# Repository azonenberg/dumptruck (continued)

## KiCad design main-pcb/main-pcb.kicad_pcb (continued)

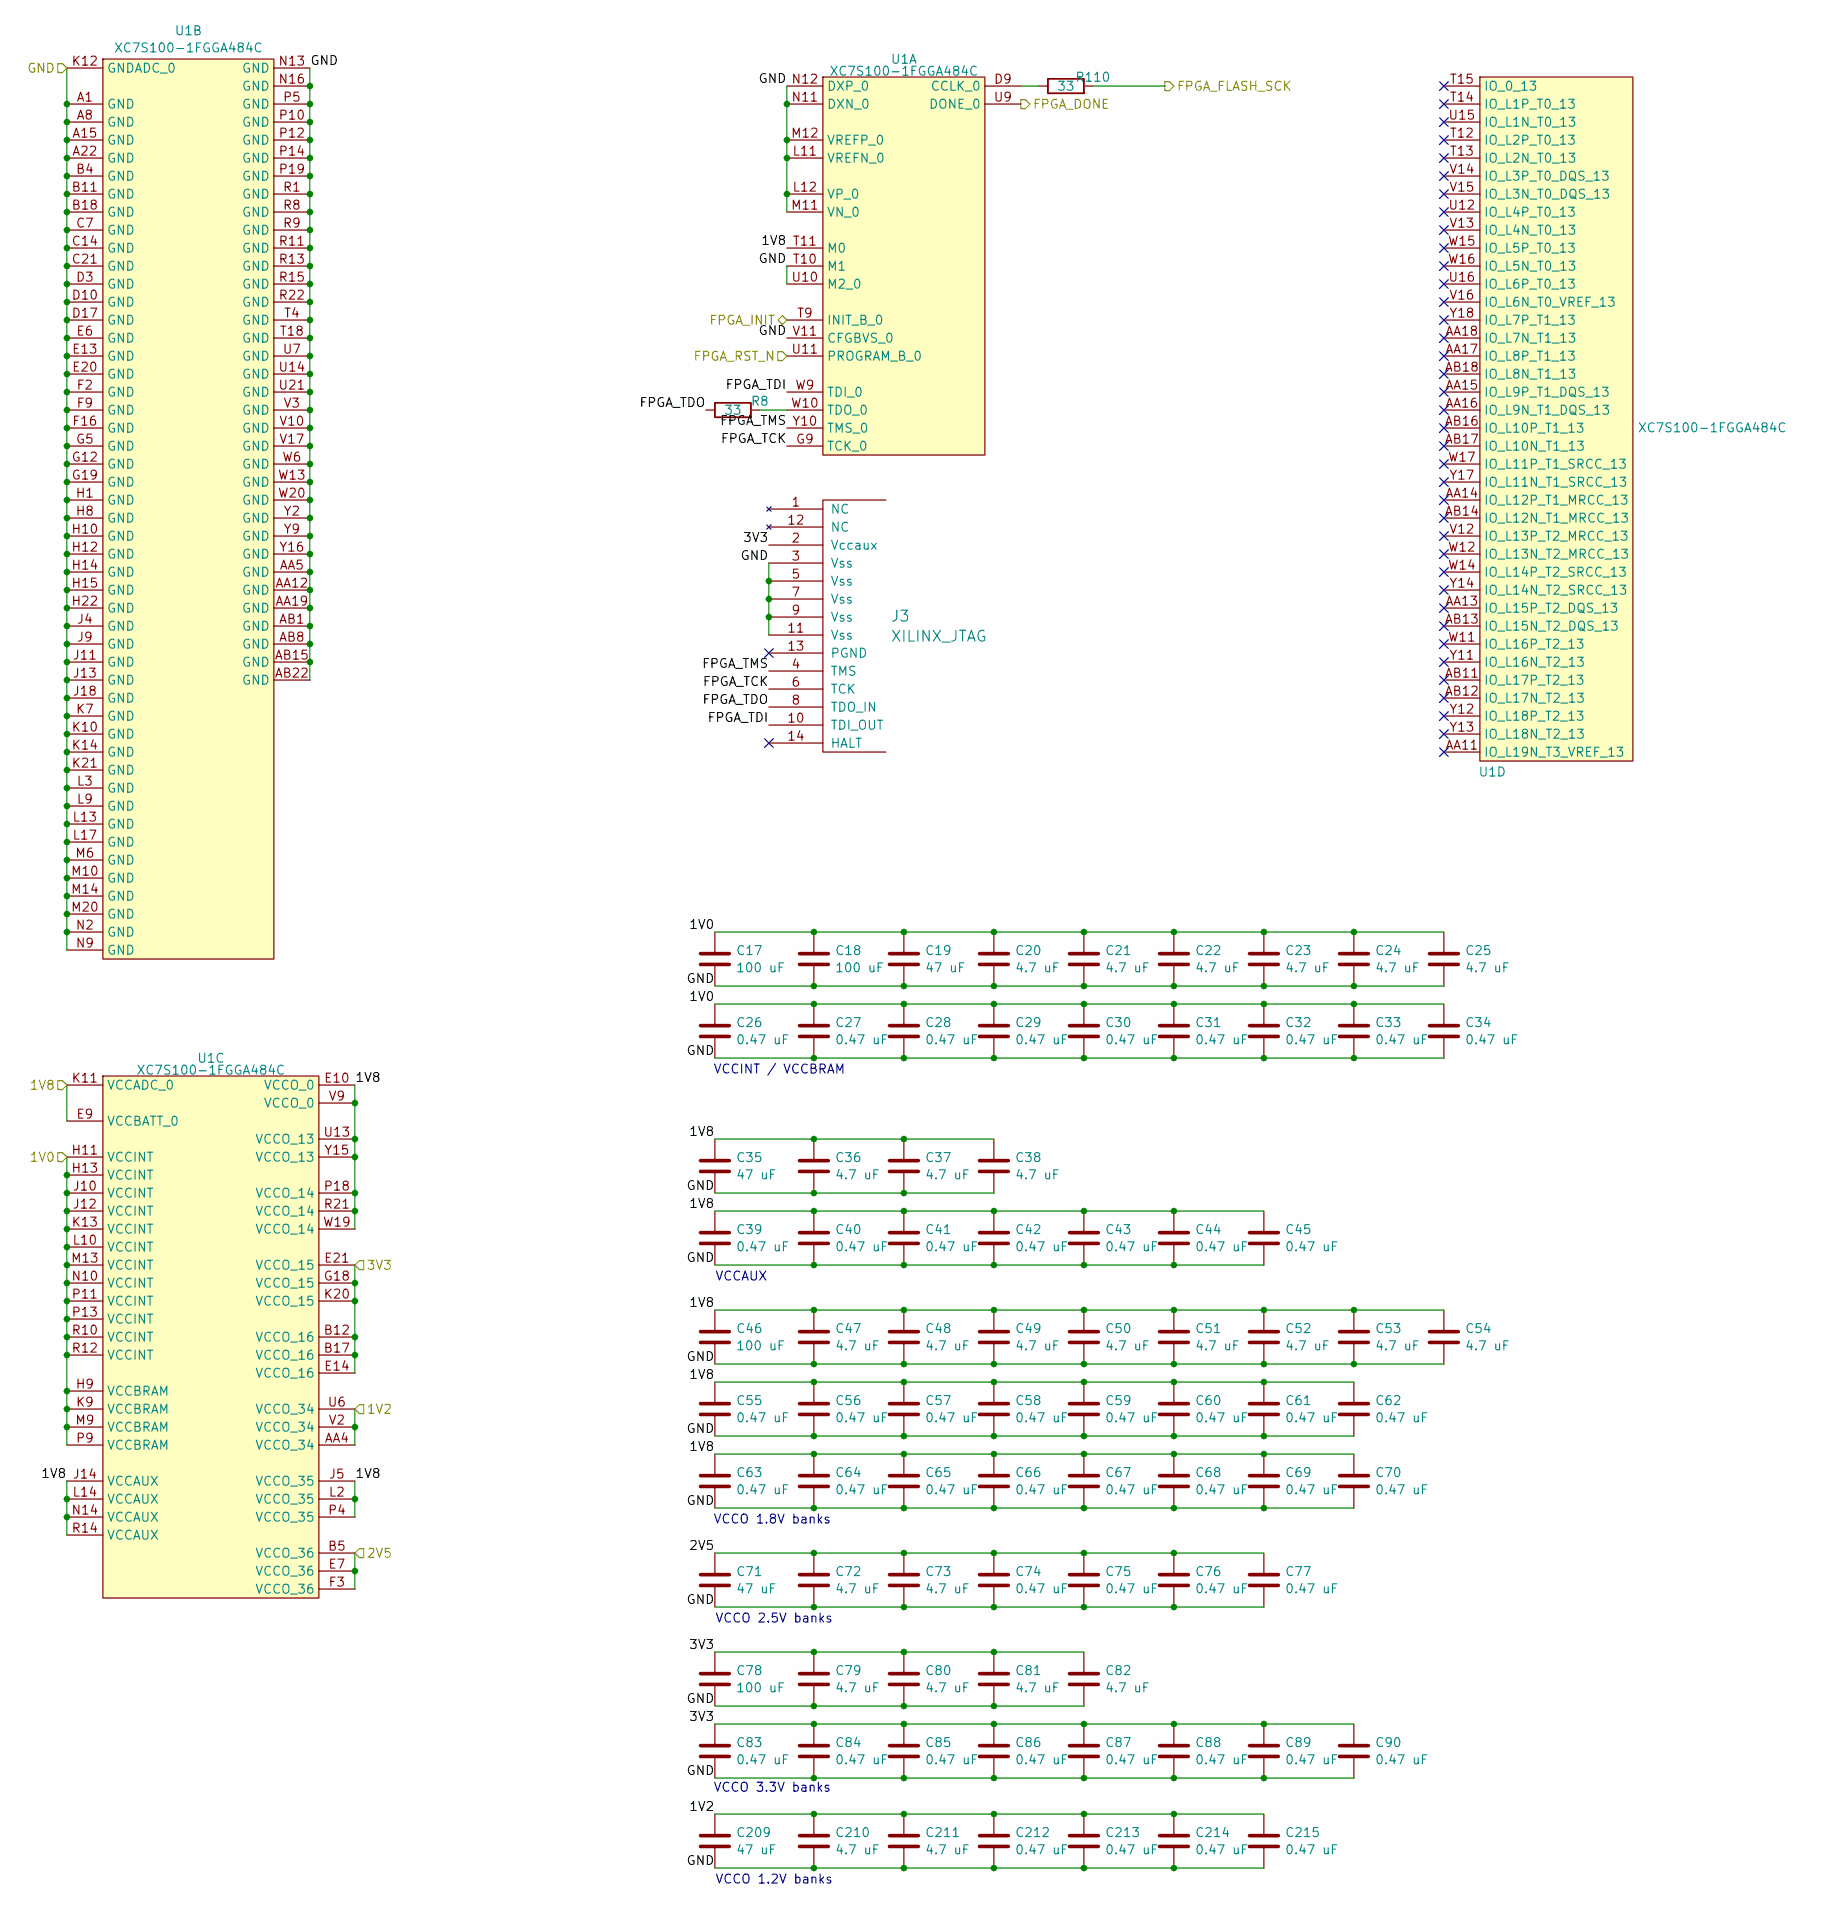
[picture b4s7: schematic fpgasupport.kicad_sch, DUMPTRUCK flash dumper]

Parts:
C17, C18, C46: 100 uF; EIA_1206_CAP_NOSILK
C19, C35, C71, C209: 47 uF; EIA_1210_CAP_NOSILK
C20, C21, C22, C23, C24, C25, C36, C37, C38, C47, C48, C49, C50, C51, C52, C53, C54, C72, C73, C79, C80, C81, C82, C210, C211: 4.7 uF; EIA_0603_CAP_NOSILK
C26, C27, C28, C29, C30, C31, C32, C33, C34, C39, C40, C41, C42, C43, C44, C45, C55, C56, C57, C58, C59, C60, C61, C62, C63, C64, C65, C66, C67, C68, C69, C70, C74, C75, C76, C77, C83, C84, C85, C86, C87, C88, C89, C90, C212, C213, C214, C215: 0.47 uF; EIA_0402_CAP_NOSILK
C78: 100 uF; EIA_1210_CAP_NOSILK
J3: XILINX_JTAG; XILINX_JTAG_PTH_MOLEX_0878311420
R8, R110: 33; EIA_0402_RES_NOSILK
U1: XC7S100-1FGGA484C; BGA_484_22x22_FULLARRAY_1MM

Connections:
/1V0: C17.1, C18.1, C19.1, C20.1, C21.1, C22.1, C23.1, C24.1, C25.1, C26.1, C27.1, C28.1, C29.1, C30.1, C31.1, C32.1, C33.1, C34.1, U1.H9 (VCCBRAM), U1.H11 (VCCINT), U1.H13 (VCCINT), U1.J10 (VCCINT), U1.J12 (VCCINT), U1.K9 (VCCBRAM), U1.K13 (VCCINT), U1.L10 (VCCINT), U1.M9 (VCCBRAM), U1.M13 (VCCINT), U1.N10 (VCCINT), U1.P9 (VCCBRAM), U1.P11 (VCCINT), U1.P13 (VCCINT), U1.R10 (VCCINT), U1.R12 (VCCINT); also elsewhere on the board
/1V2: C209.1, C210.1, C211.1, C212.1, C213.1, C214.1, C215.1, U1.AA4 (VCCO_34), U1.U6 (VCCO_34), U1.V2 (VCCO_34); also elsewhere on the board
/1V8: C35.1, C36.1, C37.1, C38.1, C39.1, C40.1, C41.1, C42.1, C43.1, C44.1, C45.1, C46.1, C47.1, C48.1, C49.1, C50.1, C51.1, C52.1, C53.1, C54.1, C55.1, C56.1, C57.1, C58.1, C59.1, C60.1, C61.1, C62.1, C63.1, C64.1, C65.1, C66.1, C67.1, C68.1, C69.1, C70.1, U1.E9 (VCCBATT_0), U1.E10 (VCCO_0), U1.J5 (VCCO_35), U1.J14 (VCCAUX), U1.K11 (VCCADC_0), U1.L2 (VCCO_35), U1.L14 (VCCAUX), U1.N14 (VCCAUX), U1.P4 (VCCO_35), U1.P18 (VCCO_14), U1.R14 (VCCAUX), U1.R21 (VCCO_14), U1.T11 (M0), U1.U13 (VCCO_13), U1.V9 (VCCO_0), U1.W19 (VCCO_14), U1.Y15 (VCCO_13); also elsewhere on the board
/2V5: C71.1, C72.1, C73.1, C74.1, C75.1, C76.1, C77.1, U1.B5 (VCCO_36), U1.E7 (VCCO_36), U1.F3 (VCCO_36); also elsewhere on the board
/3V3: C78.1, C79.1, C80.1, C81.1, C82.1, C83.1, C84.1, C85.1, C86.1, C87.1, C88.1, C89.1, C90.1, J3.2 (Vccaux), U1.B12 (VCCO_16), U1.B17 (VCCO_16), U1.E14 (VCCO_16), U1.E21 (VCCO_15), U1.G18 (VCCO_15), U1.K20 (VCCO_15); also elsewhere on the board
/FLASH_SCK: R110.2; also elsewhere on the board
/FPGA support/FPGA_INIT: U1.T9 (INIT_B_0); also elsewhere on the board
/FPGA support/FPGA_RST_N: U1.U11 (PROGRAM_B_0); also elsewhere on the board
/FPGA support/FPGA_TCK: J3.6 (TCK), U1.G9 (TCK_0)
/FPGA support/FPGA_TDI: J3.10 (TDI_OUT), U1.W9 (TDI_0)
/FPGA support/FPGA_TDO: J3.8 (TDO_IN), R8.1
/FPGA support/FPGA_TMS: J3.4 (TMS), U1.Y10 (TMS_0)
/FPGA_DONE: U1.U9 (DONE_0); also elsewhere on the board
/GND: C17.2, C18.2, C19.2, C20.2, C21.2, C22.2, C23.2, C24.2, C25.2, C26.2, C27.2, C28.2, C29.2, C30.2, C31.2, C32.2, C33.2, C34.2, C35.2, C36.2, C37.2, C38.2, C39.2, C40.2, C41.2, C42.2, C43.2, C44.2, C45.2, C46.2, C47.2, C48.2, C49.2, C50.2, C51.2, C52.2, C53.2, C54.2, C55.2, C56.2, C57.2, C58.2, C59.2, C60.2, C61.2, C62.2, C63.2, C64.2, C65.2, C66.2, C67.2, C68.2, C69.2, C70.2, C71.2, C72.2, C73.2, C74.2, C75.2, C76.2, C77.2, C78.2, C79.2, C80.2, C81.2, C82.2, C83.2, C84.2, C85.2, C86.2, C87.2, C88.2, C89.2, C90.2, C209.2, C210.2, C211.2, C212.2, C213.2, C214.2, C215.2, J3.3 (Vss), J3.5 (Vss), J3.7 (Vss), J3.9 (Vss), J3.11 (Vss), U1.A1 (GND), U1.A8 (GND), U1.A15 (GND), U1.A22 (GND), U1.AA5 (GND), U1.AA12 (GND), U1.AA19 (GND), U1.AB1 (GND), U1.AB8 (GND), U1.AB15 (GND), U1.AB22 (GND), U1.B4 (GND), U1.B11 (GND), U1.B18 (GND), U1.C7 (GND), U1.C14 (GND), U1.C21 (GND), U1.D3 (GND), U1.D10 (GND), U1.D17 (GND), U1.E6 (GND), U1.E13 (GND), U1.E20 (GND), U1.F2 (GND), U1.F9 (GND), U1.F16 (GND), U1.G5 (GND), U1.G12 (GND), U1.G19 (GND), U1.H1 (GND), U1.H8 (GND), U1.H10 (GND), U1.H12 (GND), U1.H14 (GND), U1.H15 (GND), U1.H22 (GND), U1.J4 (GND), U1.J9 (GND), U1.J11 (GND), U1.J13 (GND), U1.J18 (GND), U1.K7 (GND), U1.K10 (GND), U1.K12 (GNDADC_0), U1.K14 (GND), U1.K21 (GND), U1.L3 (GND), U1.L9 (GND), U1.L11 (VREFN_0), U1.L12 (VP_0), U1.L13 (GND), U1.L17 (GND), U1.M6 (GND), U1.M10 (GND), U1.M11 (VN_0), U1.M12 (VREFP_0), U1.M14 (GND), U1.M20 (GND), U1.N2 (GND), U1.N9 (GND), U1.N11 (DXN_0), U1.N12 (DXP_0), U1.N13 (GND), U1.N16 (GND), U1.P5 (GND), U1.P10 (GND), U1.P12 (GND), U1.P14 (GND), U1.P19 (GND), U1.R1 (GND), U1.R8 (GND), U1.R9 (GND), U1.R11 (GND), U1.R13 (GND), U1.R15 (GND), U1.R22 (GND), U1.T4 (GND), U1.T10 (M1), U1.T18 (GND), U1.U7 (GND), U1.U10 (M2_0), U1.U14 (GND), U1.U21 (GND), U1.V3 (GND), U1.V10 (GND), U1.V11 (CFGBVS_0), U1.V17 (GND), U1.W6 (GND), U1.W13 (GND), U1.W20 (GND), U1.Y2 (GND), U1.Y9 (GND), U1.Y16 (GND); also elsewhere on the board
unnamed: R110.1, U1.D9 (CCLK_0)
unnamed: R8.2, U1.W10 (TDO_0)

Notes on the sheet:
VCCO 1.2V banks
VCCO 2.5V banks
VCCAUX
VCCO 3.3V banks
VCCINT / VCCBRAM
VCCO 1.8V banks

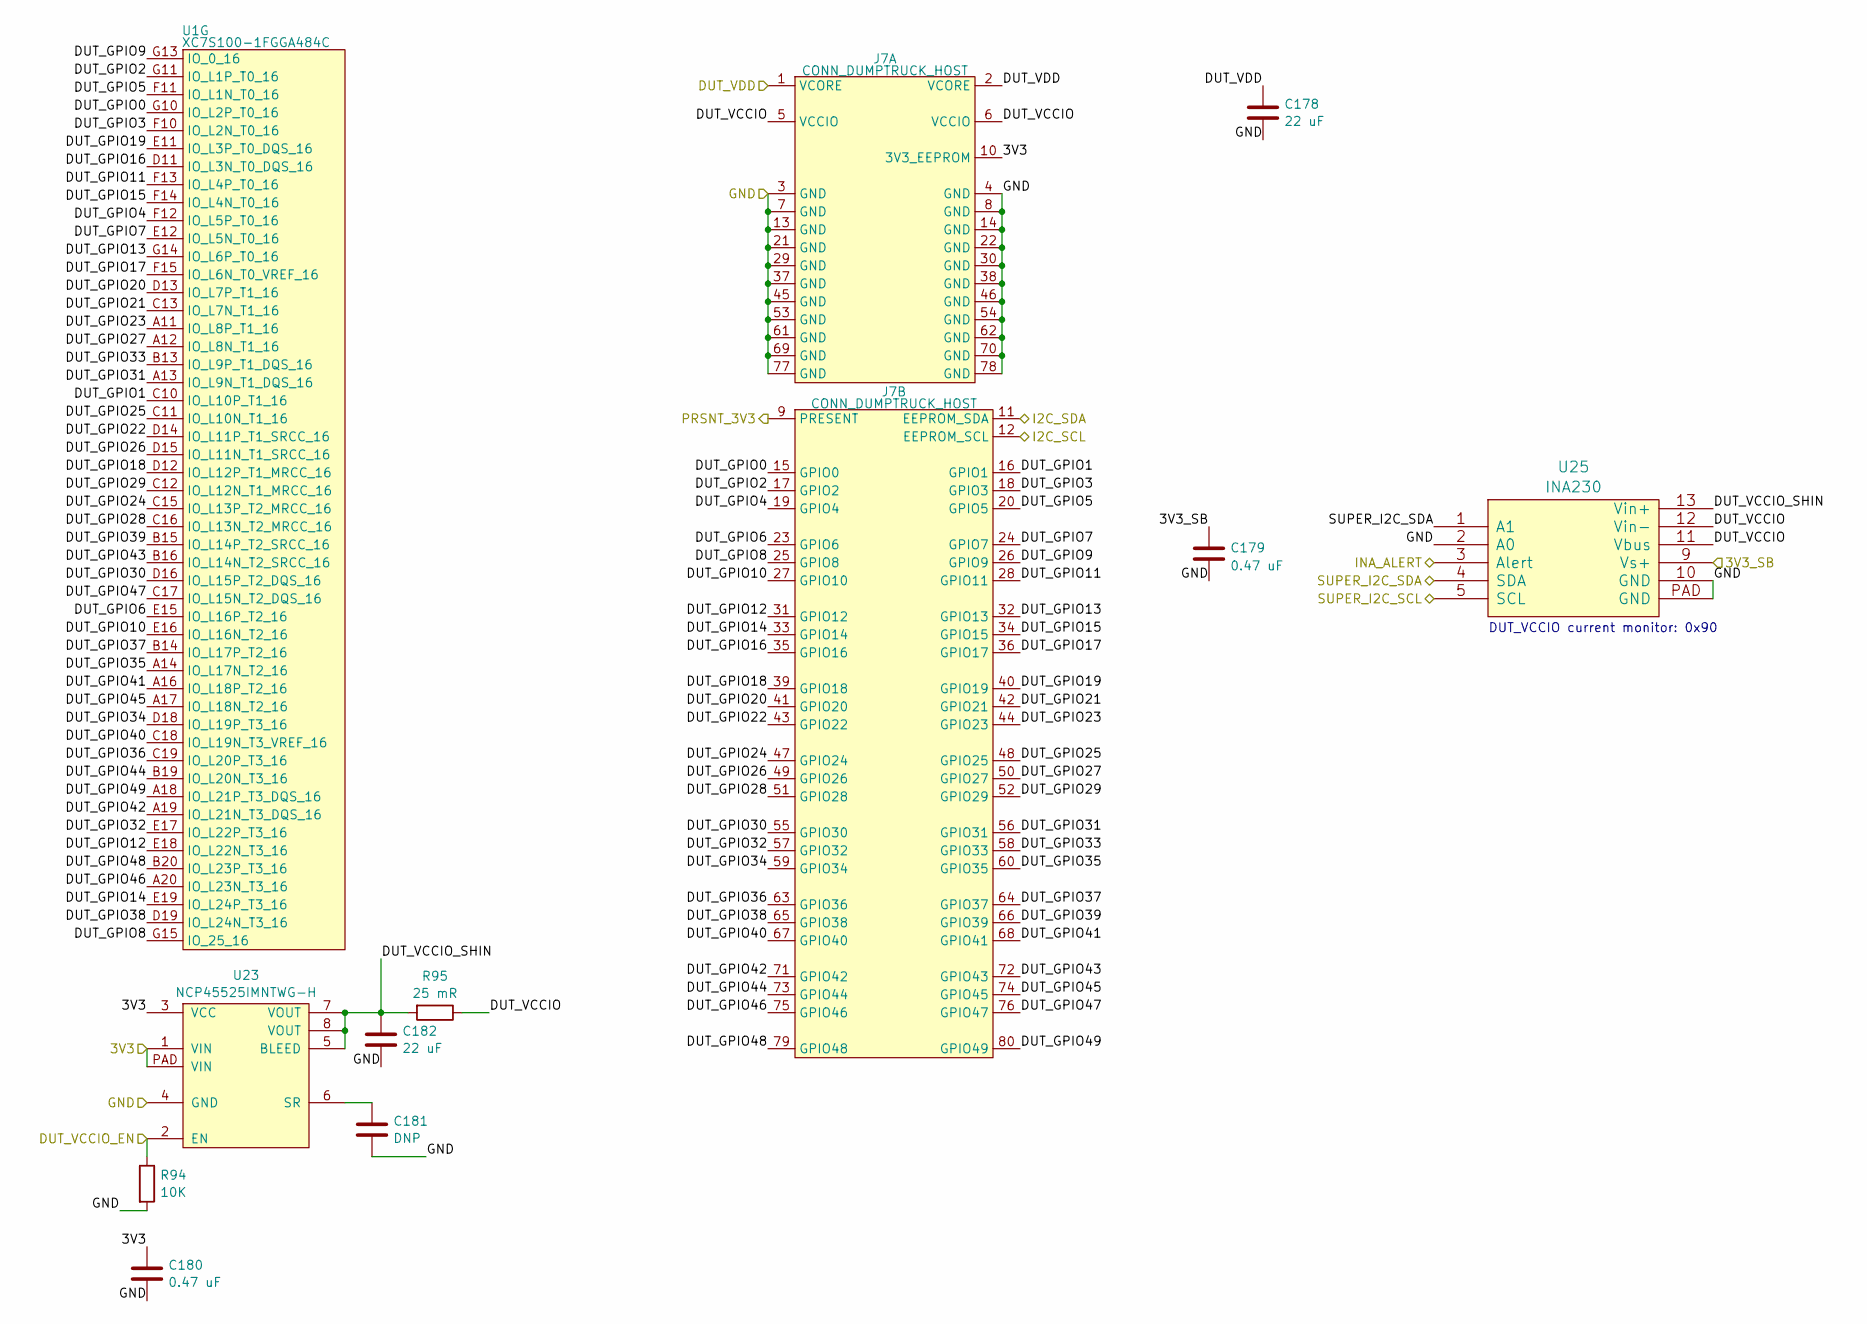
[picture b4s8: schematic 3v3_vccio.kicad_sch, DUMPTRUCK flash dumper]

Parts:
C178: 22 uF; EIA_1206_CAP_NOSILK
C179, C180: 0.47 uF; EIA_0402_CAP_NOSILK
C181: DNP; EIA_0402_CAP_NOSILK
C182: 22 uF; EIA_1210_CAP_NOSILK
J7: CONN_DUMPTRUCK_HOST; CONN_SAMTEC_BTE-040-01-F-D-A-K
R94: 10K; EIA_0402_RES_NOSILK
R95: 25 mR; EIA_0402_RES_NOSILK
U1: XC7S100-1FGGA484C; BGA_484_22x22_FULLARRAY_1MM
U23: NCP45525IMNTWG-H; DFN_8_0.5MM_2x2MM
U25: INA230; QFN_16_0.5MM_3x3MM

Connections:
/3V3: C180.1, J7.10 (3V3_EEPROM), U23.1 (VIN), U23.3 (VCC), U23.PAD (VIN); also elsewhere on the board
/3V3 VCCIO socket/DUT_GPIO0: J7.15 (GPIO0), U1.G10 (IO_L2P_T0_16)
/3V3 VCCIO socket/DUT_GPIO1: J7.16 (GPIO1), U1.C10 (IO_L10P_T1_16)
/3V3 VCCIO socket/DUT_GPIO2: J7.17 (GPIO2), U1.G11 (IO_L1P_T0_16)
/3V3 VCCIO socket/DUT_GPIO3: J7.18 (GPIO3), U1.F10 (IO_L2N_T0_16)
/3V3 VCCIO socket/DUT_GPIO4: J7.19 (GPIO4), U1.F12 (IO_L5P_T0_16)
/3V3 VCCIO socket/DUT_GPIO5: J7.20 (GPIO5), U1.F11 (IO_L1N_T0_16)
/3V3 VCCIO socket/DUT_GPIO6: J7.23 (GPIO6), U1.E15 (IO_L16P_T2_16)
/3V3 VCCIO socket/DUT_GPIO7: J7.24 (GPIO7), U1.E12 (IO_L5N_T0_16)
/3V3 VCCIO socket/DUT_GPIO8: J7.25 (GPIO8), U1.G15 (IO_25_16)
/3V3 VCCIO socket/DUT_GPIO9: J7.26 (GPIO9), U1.G13 (IO_0_16)
/3V3 VCCIO socket/DUT_GPIO10: J7.27 (GPIO10), U1.E16 (IO_L16N_T2_16)
/3V3 VCCIO socket/DUT_GPIO11: J7.28 (GPIO11), U1.F13 (IO_L4P_T0_16)
/3V3 VCCIO socket/DUT_GPIO12: J7.31 (GPIO12), U1.E18 (IO_L22N_T3_16)
/3V3 VCCIO socket/DUT_GPIO13: J7.32 (GPIO13), U1.G14 (IO_L6P_T0_16)
/3V3 VCCIO socket/DUT_GPIO14: J7.33 (GPIO14), U1.E19 (IO_L24P_T3_16)
/3V3 VCCIO socket/DUT_GPIO15: J7.34 (GPIO15), U1.F14 (IO_L4N_T0_16)
/3V3 VCCIO socket/DUT_GPIO16: J7.35 (GPIO16), U1.D11 (IO_L3N_T0_DQS_16)
/3V3 VCCIO socket/DUT_GPIO17: J7.36 (GPIO17), U1.F15 (IO_L6N_T0_VREF_16)
/3V3 VCCIO socket/DUT_GPIO18: J7.39 (GPIO18), U1.D12 (IO_L12P_T1_MRCC_16)
/3V3 VCCIO socket/DUT_GPIO19: J7.40 (GPIO19), U1.E11 (IO_L3P_T0_DQS_16)
/3V3 VCCIO socket/DUT_GPIO20: J7.41 (GPIO20), U1.D13 (IO_L7P_T1_16)
/3V3 VCCIO socket/DUT_GPIO21: J7.42 (GPIO21), U1.C13 (IO_L7N_T1_16)
/3V3 VCCIO socket/DUT_GPIO22: J7.43 (GPIO22), U1.D14 (IO_L11P_T1_SRCC_16)
/3V3 VCCIO socket/DUT_GPIO23: J7.44 (GPIO23), U1.A11 (IO_L8P_T1_16)
/3V3 VCCIO socket/DUT_GPIO24: J7.47 (GPIO24), U1.C15 (IO_L13P_T2_MRCC_16)
/3V3 VCCIO socket/DUT_GPIO25: J7.48 (GPIO25), U1.C11 (IO_L10N_T1_16)
/3V3 VCCIO socket/DUT_GPIO26: J7.49 (GPIO26), U1.D15 (IO_L11N_T1_SRCC_16)
/3V3 VCCIO socket/DUT_GPIO27: J7.50 (GPIO27), U1.A12 (IO_L8N_T1_16)
/3V3 VCCIO socket/DUT_GPIO28: J7.51 (GPIO28), U1.C16 (IO_L13N_T2_MRCC_16)
/3V3 VCCIO socket/DUT_GPIO29: J7.52 (GPIO29), U1.C12 (IO_L12N_T1_MRCC_16)
/3V3 VCCIO socket/DUT_GPIO30: J7.55 (GPIO30), U1.D16 (IO_L15P_T2_DQS_16)
/3V3 VCCIO socket/DUT_GPIO31: J7.56 (GPIO31), U1.A13 (IO_L9N_T1_DQS_16)
/3V3 VCCIO socket/DUT_GPIO32: J7.57 (GPIO32), U1.E17 (IO_L22P_T3_16)
/3V3 VCCIO socket/DUT_GPIO33: J7.58 (GPIO33), U1.B13 (IO_L9P_T1_DQS_16)
/3V3 VCCIO socket/DUT_GPIO34: J7.59 (GPIO34), U1.D18 (IO_L19P_T3_16)
/3V3 VCCIO socket/DUT_GPIO35: J7.60 (GPIO35), U1.A14 (IO_L17N_T2_16)
/3V3 VCCIO socket/DUT_GPIO36: J7.63 (GPIO36), U1.C19 (IO_L20P_T3_16)
/3V3 VCCIO socket/DUT_GPIO37: J7.64 (GPIO37), U1.B14 (IO_L17P_T2_16)
/3V3 VCCIO socket/DUT_GPIO38: J7.65 (GPIO38), U1.D19 (IO_L24N_T3_16)
/3V3 VCCIO socket/DUT_GPIO39: J7.66 (GPIO39), U1.B15 (IO_L14P_T2_SRCC_16)
/3V3 VCCIO socket/DUT_GPIO40: J7.67 (GPIO40), U1.C18 (IO_L19N_T3_VREF_16)
/3V3 VCCIO socket/DUT_GPIO41: J7.68 (GPIO41), U1.A16 (IO_L18P_T2_16)
/3V3 VCCIO socket/DUT_GPIO42: J7.71 (GPIO42), U1.A19 (IO_L21N_T3_DQS_16)
/3V3 VCCIO socket/DUT_GPIO43: J7.72 (GPIO43), U1.B16 (IO_L14N_T2_SRCC_16)
/3V3 VCCIO socket/DUT_GPIO44: J7.73 (GPIO44), U1.B19 (IO_L20N_T3_16)
/3V3 VCCIO socket/DUT_GPIO45: J7.74 (GPIO45), U1.A17 (IO_L18N_T2_16)
/3V3 VCCIO socket/DUT_GPIO46: J7.75 (GPIO46), U1.A20 (IO_L23N_T3_16)
/3V3 VCCIO socket/DUT_GPIO47: J7.76 (GPIO47), U1.C17 (IO_L15N_T2_DQS_16)
/3V3 VCCIO socket/DUT_GPIO48: J7.79 (GPIO48), U1.B20 (IO_L23P_T3_16)
/3V3 VCCIO socket/DUT_GPIO49: J7.80 (GPIO49), U1.A18 (IO_L21P_T3_DQS_16)
/3V3 VCCIO socket/DUT_VCCIO: J7.5 (VCCIO), J7.6 (VCCIO), R95.1, U25.11 (Vbus), U25.12 (Vin-)
/3V3 VCCIO socket/DUT_VCCIO_SHIN: C182.1, R95.2, U23.5 (BLEED), U23.7 (VOUT), U23.8 (VOUT), U25.13 (Vin+)
/3V3_SB: C179.1, U25.9 (Vs+); also elsewhere on the board
/DUT_VCCIO_EN: R94.1, U23.2 (EN); also elsewhere on the board
/DUT_VDD: C178.1, J7.1 (VCORE), J7.2 (VCORE); also elsewhere on the board
/GND: C178.2, C179.2, C180.2, C181.2, C182.2, J7.3 (GND), J7.4 (GND), J7.7 (GND), J7.8 (GND), J7.13 (GND), J7.14 (GND), J7.21 (GND), J7.22 (GND), J7.29 (GND), J7.30 (GND), J7.37 (GND), J7.38 (GND), J7.45 (GND), J7.46 (GND), J7.53 (GND), J7.54 (GND), J7.61 (GND), J7.62 (GND), J7.69 (GND), J7.70 (GND), J7.77 (GND), J7.78 (GND), R94.2, U23.4 (GND), U25.2 (A0), U25.10 (GND), U25.PAD (GND); also elsewhere on the board
/I2C_SCL: J7.12 (EEPROM_SCL); also elsewhere on the board
/I2C_SDA: J7.11 (EEPROM_SDA); also elsewhere on the board
/INA_ALERT: U25.3 (Alert); also elsewhere on the board
/PRSNT_3V3: J7.9 (PRESENT); also elsewhere on the board
/SUPER_I2C_SCL: U25.5 (SCL); also elsewhere on the board
/SUPER_I2C_SDA: U25.1 (A1), U25.4 (SDA); also elsewhere on the board
unnamed: C181.1, U23.6 (SR)

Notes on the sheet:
DUT_VCCIO current monitor: 0x90

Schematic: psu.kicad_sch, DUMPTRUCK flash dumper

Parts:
C1, C4, C5, C6, C7, C8, C9, C10, C11, C12, C13, C14, C15, C94, C97, C98, C101, C167, C170, C172, C173, C175, C176: 0.47 uF; EIA_0402_CAP_NOSILK
C2: 4.7 uF; EIA_0603_CAP_NOSILK
C3: 0.1 uF; EIA_0402_CAP_NOSILK
C16, C93, C99, C171: 22 uF; EIA_1210_CAP_NOSILK
C91, C96: 10 uF; EIA_1210_CAP_NOSILK
C92, C174: 47 uF; EIA_1210_CAP_NOSILK
C95, C135: 22 uF; EIA_1206_CAP_NOSILK
C100, C166, C169: 10 uF; EIA_1206_CAP_NOSILK
C168: 22 uF; EIA_0805_CAP_NOSILK
C177: DNP; EIA_0402_CAP_NOSILK
D1, D2: GREEN; EIA_0402_LED
D3: RED; EIA_0402_LED
FB1: MI0603J601R-10; EIA_0603_INDUCTOR_NOSILK
J1: CONN_01X03; CONN_HEADER_2.54MM_1x3
J2: CORTEX_DEBUG_ETM; CONN_HEADER_1.27MM_2x10_SMT_SAMTEC_FTSH-110-01-L-DV-K
JP1, JP2, JP3, JP4: Jumper; CONN_HEADER_2.54MM_1x2
L1, L2, L3, L5, L6, L7: 2.2 uH; EIA_1210_CAP_NOSILK
R1: DNP; EIA_0402_RES_NOSILK
R2, R3: 33K; EIA_0402_RES_NOSILK
R4, R36, R40: 4.7K; EIA_0402_RES_NOSILK
R5, R13, R14, R15, R18, R19, R20, R77, R78, R79, R83, R84, R85, R88, R89, R90, R92: 10K; EIA_0402_RES_NOSILK
R6: 1K; EIA_0402_RES_NOSILK
R7: 33; EIA_0402_RES_NOSILK
R9, R21, R22, R23, R76, R80, R91, R93: 25 mR; EIA_0402_RES_NOSILK
R10: 0; EIA_0402_RES_NOSILK
R11, R16, R24: 280K; EIA_0402_RES_NOSILK
R12, R25: 88.7K; EIA_0402_RES_NOSILK
R17: 130K; EIA_0402_RES_NOSILK
R46, R81: 232K; EIA_0402_RES_NOSILK
R75: 187K; EIA_0402_RES_NOSILK
R82: 464K; EIA_0402_RES_NOSILK
R86: 255K; EIA_0402_RES_NOSILK
R87: 1.02M; EIA_0402_RES_NOSILK
SW1, SW2: SWITCH; SWITCH_RAFI_MICON_5
TP1, TP2, TP3, TP4, TP12, TP13, TP14, TP16: U.FL; CONN_U.FL_TE_1909763-1
TP15: CONN_01X08; CONN_HEADER_2.54MM_1x8
U2: STM32L431-QFN48; QFN_48_0.5MM_7x7MM
U3, U4, U5, U6, U7, U8, U9, U19: INA230; QFN_16_0.5MM_3x3MM
U10: NCP45525IMNTWG-H; DFN_8_0.5MM_2x2MM
U11: LTC3374-QFN; QFN_38_0.5MM_5x7MM

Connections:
/1V0: R86.1, R88.1, R91.1, TP14.1 (In), U19.11 (Vbus), U19.12 (Vin-); also elsewhere on the board
/1V2: JP4.1, R80.1, R81.1, R83.1, TP13.1 (In), U8.11 (Vbus), U8.12 (Vin-); also elsewhere on the board
/1V8: JP3.1, R46.1, R76.1, R77.1, TP12.1 (In), U7.11 (Vbus), U7.12 (Vin-); also elsewhere on the board
/2V5: JP2.1, R16.1, R18.1, R22.1, TP3.1 (In), U6.11 (Vbus), U6.12 (Vin-); also elsewhere on the board
/3V3: C176.1, JP1.1, R11.1, R13.1, R21.1, TP1.1 (In), U5.11 (Vbus), U5.12 (Vin-), U10.3 (VCC); also elsewhere on the board
/3V3_SB: C1.1, C2.1, C4.1, C6.1, C7.1, C8.1, C9.1, C10.1, C11.1, C12.1, C13.1, C14.1, C15.1, C175.1, FB1.2, J2.1 (VCC), R1.1, R6.1, R23.1, R24.1, R36.1, R40.1, SW1.2, SW2.2, TP4.1 (In), U2.1 (VBAT), U2.24 (VDD), U2.36 (VDD), U2.48 (VDD), U3.9 (Vs+), U4.2 (A0), U4.9 (Vs+), U4.11 (Vbus), U4.12 (Vin-), U5.9 (Vs+), U6.9 (Vs+), U7.1 (A1), U7.9 (Vs+), U8.1 (A1), U8.2 (A0), U8.9 (Vs+), U9.1 (A1), U9.9 (Vs+), U19.1 (A1), U19.9 (Vs+); also elsewhere on the board
/DUT_VCCIO_EN: TP15.4, U2.33 (PA12); also elsewhere on the board
/DUT_VDD: R93.1, TP16.1 (In), U9.11 (Vbus), U9.12 (Vin-); also elsewhere on the board
/FPGA support/FPGA_INIT: U2.28 (PB15); also elsewhere on the board
/FPGA support/FPGA_RST_N: U2.29 (PA8); also elsewhere on the board
/FPGA_DONE: U2.32 (PA11); also elsewhere on the board
/GND: C1.2, C2.2, C3.2, C4.2, C5.2, C6.2, C7.2, C8.2, C9.2, C10.2, C11.2, C12.2, C13.2, C14.2, C15.2, C16.2, C91.2, C92.2, C93.2, C94.2, C95.2, C96.2, C97.2, C98.2, C99.2, C100.2, C101.2, C135.2, C166.2, C167.2, C168.2, C169.2, C170.2, C171.2, C172.2, C173.2, C174.2, C175.2, C176.2, C177.2, D1.1 (K), D2.1 (K), D3.1 (K), J1.3, J2.3 (GND), J2.5 (GND), J2.9 (GNDdet), J2.11 (GND), J2.13 (GND), J2.15 (GND), J2.17 (GND), J2.19 (GND), R5.2, R10.2, R12.2, R14.2, R15.2, R17.2, R19.2, R20.2, R25.2, R75.2, R78.2, R79.2, R82.2, R84.2, R85.2, R87.2, R89.2, R90.2, R92.2, TP1.2 (Ext), TP2.2 (Ext), TP3.2 (Ext), TP4.2 (Ext), TP12.2 (Ext), TP13.2 (Ext), TP14.2 (Ext), TP15.1, TP15.8, TP16.2 (Ext), U2.8 (VSSA), U2.23 (GND), U2.35 (GND), U2.47 (GND), U2.PAD (GND), U3.1 (A1), U3.2 (A0), U3.10 (GND), U3.PAD (GND), U4.1 (A1), U4.10 (GND), U4.PAD (GND), U5.1 (A1), U5.10 (GND), U5.PAD (GND), U6.1 (A1), U6.10 (GND), U6.PAD (GND), U7.2 (A0), U7.10 (GND), U7.PAD (GND), U8.10 (GND), U8.PAD (GND), U9.10 (GND), U9.PAD (GND), U10.4 (GND), U11.16 (SYNC), U11.32 (EN8), U11.37 (EN2), U11.PAD (GND), U19.10 (GND), U19.PAD (GND); also elsewhere on the board
/INA_ALERT: TP15.5, U2.41 (PB5), U3.3 (Alert), U4.3 (Alert), U5.3 (Alert), U6.3 (Alert), U7.3 (Alert), U8.3 (Alert), U9.3 (Alert), U19.3 (Alert); also elsewhere on the board
/MCU/MCU_RST_N: U2.25 (PB12); also elsewhere on the board
/MCU/SUPER_SPI_CS_N: U2.14 (SPI1_NSS); also elsewhere on the board
/MCU/SUPER_SPI_MISO: U2.16 (SPI1_MISO); also elsewhere on the board
/MCU/SUPER_SPI_MOSI: U2.17 (SPI1_MOSI); also elsewhere on the board
/MCU/SUPER_SPI_SCK: U2.15 (SPI1_SCK); also elsewhere on the board
/Power supply/1V0_DIV2: R88.2, R89.1, U2.19 (ADC1_IN16)
/Power supply/1V0_EN: R90.1, U2.6 (PH1), U11.33 (EN7)
/Power supply/1V0_FB: R86.2, R87.1, U11.26 (FB7)
/Power supply/1V0_SHIN: C174.1, L7.1, R91.2, U19.13 (Vin+)
/Power supply/1V0_SW: L7.2, U11.28 (SW7), U11.29 (SW8)
/Power supply/1V2_DIV2: R83.2, R84.1, U2.13 (ADC1_IN8)
/Power supply/1V2_EN: R85.1, U2.21 (PB10), U11.18 (EN6)
/Power supply/1V2_FB: R81.2, R82.1, U11.25 (FB6)
/Power supply/1V2_SHIN: C168.1, L6.1, R80.2, U8.13 (Vin+)
/Power supply/1V8_DIV2: R77.2, R78.1, U2.18 (ADC1_IN15)
/Power supply/1V8_EN: R79.1, U2.20 (PB2), U11.19 (EN5)
/Power supply/1V8_FB: R46.2, R75.1, U11.20 (FB5)
/Power supply/1V8_SHIN: C135.1, L5.1, R76.2, U7.13 (Vin+)
/Power supply/2V5_DIV2: R18.2, R19.1, U2.12 (ADC1_IN7)
/Power supply/2V5_EN: R20.1, U2.2 (PC13), U11.14 (EN3)
/Power supply/2V5_FB: R16.2, R17.1, U11.7 (FB3)
/Power supply/2V5_SHIN: C95.1, L2.1, R22.2, U6.13 (Vin+)
/Power supply/3V3_DIV2: R13.2, R14.1, U2.11 (ADC1_IN6)
/Power supply/3V3_EN: R15.1, U2.4 (PC15), U11.38 (EN1)
/Power supply/3V3_FB: R11.2, R12.1, U11.1 (FB1)
/Power supply/3V3_SB_FB: R24.2, R25.1, U11.12 (FB4)
/Power supply/3V3_SB_SHIN: C99.1, L3.1, R23.2, U4.13 (Vin+)
/Power supply/3V3_SHIN: C92.1, L1.1, R21.2, U5.13 (Vin+)
/Power supply/3V3_SW: L1.2, U11.3 (SW1), U11.4 (SW2)
/Power supply/A3V3_SUPER: C5.1, FB1.1, U2.9 (VDDA)
/Power supply/DUT_VDD_EN: R92.1, TP15.3, U2.3 (PC14), U10.2 (EN)
/Power supply/DUT_VDD_RAW: JP1.2, JP2.2, JP3.2, JP4.2, U10.1 (VIN), U10.PAD (VIN)
/Power supply/DUT_VDD_SHIN: C16.1, R93.2, U9.13 (Vin+), U10.5 (BLEED), U10.7 (VOUT), U10.8 (VOUT)
/Power supply/LTC_PGOOD_ALL: TP15.2, U2.22 (PB11), U11.15 (PGOOD_ALL)
/Power supply/LTC_VTEMP: U2.10 (ADC1_IN5), U11.36 (TEMP)
/Power supply/SOFT_PWR: SW1.1, U2.26 (PB13)
/Power supply/SOFT_RST: SW2.1, U2.27 (PB14)
/Power supply/SUPER_BOOT0: R5.1, U2.44 (BOOT0)
/Power supply/SUPER_FAULT_LED: R4.1, U2.45 (PB8)
/Power supply/SUPER_JTAG_TCK: J2.4 (TCK), U2.37 (JTCK)
/Power supply/SUPER_JTAG_TDI: J2.8 (TDI), U2.38 (JTDI)
/Power supply/SUPER_JTAG_TDO: J2.6 (TDO), R7.1
/Power supply/SUPER_JTAG_TMS: J2.2 (TMS), U2.34 (JTMS)
/Power supply/SUPER_JTAG_TRST: R6.2, U2.40 (NJTRST)
/Power supply/SUPER_PWRGOOD_LED: R2.1, U2.46 (PB9)
/Power supply/SUPER_RST_N: C3.1, J2.10 (~RST), R1.2, U2.7 (NRST)
/Power supply/SUPER_SYSOK_LED: R3.1, U2.5 (PH0)
/Power supply/SUPER_UART_RX: J1.1, U2.31 (USART1_RX)
/Power supply/SUPER_UART_TX: J1.2, U2.30 (USART1_TX)
/SUPER_I2C_SCL: R36.2, TP15.7, U2.42 (I2C1_SCL), U3.5 (SCL), U4.5 (SCL), U5.5 (SCL), U6.2 (A0), U6.5 (SCL), U7.5 (SCL), U8.5 (SCL), U9.2 (A0), U9.5 (SCL), U19.5 (SCL); also elsewhere on the board
/SUPER_I2C_SDA: R40.2, TP15.6, U2.43 (I2C1_SDA), U3.4 (SDA), U4.4 (SDA), U5.2 (A0), U5.4 (SDA), U6.4 (SDA), U7.4 (SDA), U8.4 (SDA), U9.4 (SDA), U19.2 (A0), U19.4 (SDA); also elsewhere on the board
/VBUS: R9.2, U3.13 (Vin+); also elsewhere on the board
/VBUS_SHOUT: C91.1, C93.1, C94.1, C96.1, C97.1, C98.1, C100.1, C101.1, C166.1, C167.1, C169.1, C170.1, C171.1, C172.1, C173.1, R9.1, TP2.1 (In), U3.11 (Vbus), U3.12 (Vin-), U11.2 (VIN1), U11.5 (VIN2), U11.6 (FB2), U11.8 (VIN3), U11.11 (VIN4), U11.13 (EN4), U11.17 (RT), U11.21 (VIN5), U11.24 (VIN6), U11.27 (VIN7), U11.30 (VIN8), U11.31 (FB8), U11.35 (VCC); also elsewhere on the board
unnamed: D1.2 (A), R2.2
unnamed: D2.2 (A), R3.2
unnamed: D3.2 (A), R4.2
unnamed: R7.2, U2.39 (JTDO)
unnamed: C177.1, U10.6 (SR)
unnamed: L2.2, U11.9 (SW3)
unnamed: L3.2, U11.10 (SW4)
unnamed: L5.2, U11.22 (SW5)
unnamed: L6.2, U11.23 (SW6)
unnamed: R10.1, U11.34 (MODE)

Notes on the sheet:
3V3 current monitor: 0x84
VBUS current monitor: 0x80
3V3_SB current monitor: 0x82
DUT_VDD current monitor: 0x8e
2V5 current monitor: 0x86
1V0 current monitor: 0x8c
1V2 current monitor: 0x8a
1V8 current monitor: 0x88
Use divided rails as ADC inputs for sequencing decisions and system safety checks only Use INA230 (slower but more accurate) for anything not time critical
Aim for 25 mV drop on shunts at 1A load? That's 25 milliohms

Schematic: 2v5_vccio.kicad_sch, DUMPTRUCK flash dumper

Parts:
C183, C186: 0.47 uF; EIA_0402_CAP_NOSILK
C184: DNP; EIA_0402_CAP_NOSILK
C185, C187: 22 uF; EIA_1206_CAP_NOSILK
J8: CONN_DUMPTRUCK_HOST; CONN_SAMTEC_BTE-040-01-F-D-A-K
R96: DNP; EIA_0402_RES_NOSILK
R97: 25 mR; EIA_0402_RES_NOSILK
U1: XC7S100-1FGGA484C; BGA_484_22x22_FULLARRAY_1MM
U27: NCP45525IMNTWG-H; DFN_8_0.5MM_2x2MM
U28: INA230; QFN_16_0.5MM_3x3MM

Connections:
/2V5: U27.1 (VIN), U27.PAD (VIN); also elsewhere on the board
/2V5 VCCIO socket/DUT_GPIO0: J8.15 (GPIO0), U1.G8 (IO_L9P_T1_DQS_36)
/2V5 VCCIO socket/DUT_GPIO1: J8.16 (GPIO1), U1.G7 (IO_L11P_T1_SRCC_36)
/2V5 VCCIO socket/DUT_GPIO2: J8.17 (GPIO2), U1.F6 (IO_L12N_T1_MRCC_36)
/2V5 VCCIO socket/DUT_GPIO3: J8.18 (GPIO3), U1.G6 (IO_L11N_T1_SRCC_36)
/2V5 VCCIO socket/DUT_GPIO4: J8.19 (GPIO4), U1.F7 (IO_L12P_T1_MRCC_36)
/2V5 VCCIO socket/DUT_GPIO5: J8.20 (GPIO5), U1.G3 (IO_L19N_T3_VREF_36)
/2V5 VCCIO socket/DUT_GPIO6: J8.23 (GPIO6), U1.F8 (IO_L9N_T1_DQS_36)
/2V5 VCCIO socket/DUT_GPIO7: J8.24 (GPIO7), U1.G4 (IO_L19P_T3_36)
/2V5 VCCIO socket/DUT_GPIO8: J8.25 (GPIO8), U1.D6 (IO_L8P_T1_36)
/2V5 VCCIO socket/DUT_GPIO9: J8.26 (GPIO9), U1.F4 (IO_25_36)
/2V5 VCCIO socket/DUT_GPIO10: J8.27 (GPIO10), U1.C6 (IO_L7P_T1_36)
/2V5 VCCIO socket/DUT_GPIO11: J8.28 (GPIO11), U1.E4 (IO_L20P_T3_36)
/2V5 VCCIO socket/DUT_GPIO12: J8.31 (GPIO12), U1.D7 (IO_L6N_T0_VREF_36)
/2V5 VCCIO socket/DUT_GPIO13: J8.32 (GPIO13), U1.E5 (IO_L10N_T1_36)
/2V5 VCCIO socket/DUT_GPIO14: J8.33 (GPIO14), U1.D8 (IO_L6P_T0_36)
/2V5 VCCIO socket/DUT_GPIO15: J8.34 (GPIO15), U1.D4 (IO_L20N_T3_36)
/2V5 VCCIO socket/DUT_GPIO16: J8.35 (GPIO16), U1.C8 (IO_L3N_T0_DQS_36)
/2V5 VCCIO socket/DUT_GPIO17: J8.36 (GPIO17), U1.D5 (IO_L8N_T1_36)
/2V5 VCCIO socket/DUT_GPIO18: J8.39 (GPIO18), U1.E8 (IO_0_36)
/2V5 VCCIO socket/DUT_GPIO19: J8.40 (GPIO19), U1.F5 (IO_L10P_T1_36)
/2V5 VCCIO socket/DUT_GPIO20: J8.41 (GPIO20), U1.C9 (IO_L3P_T0_DQS_36)
/2V5 VCCIO socket/DUT_GPIO21: J8.42 (GPIO21), U1.A3 (IO_L14N_T2_SRCC_36)
/2V5 VCCIO socket/DUT_GPIO22: J8.43 (GPIO22), U1.C3 (IO_L16N_T2_36)
/2V5 VCCIO socket/DUT_GPIO23: J8.44 (GPIO23), U1.B3 (IO_L15P_T2_DQS_36)
/2V5 VCCIO socket/DUT_GPIO24: J8.47 (GPIO24), U1.A4 (IO_L14P_T2_SRCC_36)
/2V5 VCCIO socket/DUT_GPIO25: J8.48 (GPIO25), U1.A2 (IO_L15N_T2_DQS_36)
/2V5 VCCIO socket/DUT_GPIO26: J8.49 (GPIO26), U1.C4 (IO_L16P_T2_36)
/2V5 VCCIO socket/DUT_GPIO27: J8.50 (GPIO27), U1.G1 (IO_L22N_T3_36)
/2V5 VCCIO socket/DUT_GPIO28: J8.51 (GPIO28), U1.A5 (IO_L13N_T2_MRCC_36)
/2V5 VCCIO socket/DUT_GPIO29: J8.52 (GPIO29), U1.G2 (IO_L22P_T3_36)
/2V5 VCCIO socket/DUT_GPIO30: J8.55 (GPIO30), U1.B10 (IO_L2P_T0_36)
/2V5 VCCIO socket/DUT_GPIO31: J8.56 (GPIO31), U1.F1 (IO_L21P_T3_DQS_36)
/2V5 VCCIO socket/DUT_GPIO32: J8.57 (GPIO32), U1.A10 (IO_L2N_T0_36)
/2V5 VCCIO socket/DUT_GPIO33: J8.58 (GPIO33), U1.E2 (IO_L24P_T3_36)
/2V5 VCCIO socket/DUT_GPIO34: J8.59 (GPIO34), U1.B9 (IO_L1P_T0_36)
/2V5 VCCIO socket/DUT_GPIO35: J8.60 (GPIO35), U1.E1 (IO_L21N_T3_DQS_36)
/2V5 VCCIO socket/DUT_GPIO36: J8.63 (GPIO36), U1.A9 (IO_L1N_T0_36)
/2V5 VCCIO socket/DUT_GPIO37: J8.64 (GPIO37), U1.E3 (IO_L23P_T3_36)
/2V5 VCCIO socket/DUT_GPIO38: J8.65 (GPIO38), U1.B8 (IO_L5P_T0_36)
/2V5 VCCIO socket/DUT_GPIO39: J8.66 (GPIO39), U1.D1 (IO_L24N_T3_36)
/2V5 VCCIO socket/DUT_GPIO40: J8.67 (GPIO40), U1.B7 (IO_L5N_T0_36)
/2V5 VCCIO socket/DUT_GPIO41: J8.68 (GPIO41), U1.D2 (IO_L23N_T3_36)
/2V5 VCCIO socket/DUT_GPIO42: J8.71 (GPIO42), U1.A7 (IO_L4P_T0_36)
/2V5 VCCIO socket/DUT_GPIO43: J8.72 (GPIO43), U1.C1 (IO_L18N_T2_36)
/2V5 VCCIO socket/DUT_GPIO44: J8.73 (GPIO44), U1.B6 (IO_L13P_T2_MRCC_36)
/2V5 VCCIO socket/DUT_GPIO45: J8.74 (GPIO45), U1.C2 (IO_L18P_T2_36)
/2V5 VCCIO socket/DUT_GPIO46: J8.75 (GPIO46), U1.A6 (IO_L4N_T0_36)
/2V5 VCCIO socket/DUT_GPIO47: J8.76 (GPIO47), U1.B1 (IO_L17N_T2_36)
/2V5 VCCIO socket/DUT_GPIO48: J8.79 (GPIO48), U1.C5 (IO_L7N_T1_36)
/2V5 VCCIO socket/DUT_GPIO49: J8.80 (GPIO49), U1.B2 (IO_L17P_T2_36)
/2V5 VCCIO socket/DUT_VCCIO: J8.5 (VCCIO), J8.6 (VCCIO), R97.1, U28.11 (Vbus), U28.12 (Vin-)
/2V5 VCCIO socket/DUT_VCCIO_SHIN: C185.1, R97.2, U27.5 (BLEED), U27.7 (VOUT), U27.8 (VOUT), U28.13 (Vin+)
/3V3: C183.1, J8.10 (3V3_EEPROM), U27.3 (VCC); also elsewhere on the board
/3V3_SB: C186.1, U28.2 (A0), U28.9 (Vs+); also elsewhere on the board
/DUT_VCCIO_EN: R96.1, U27.2 (EN); also elsewhere on the board
/DUT_VDD: C187.1, J8.1 (VCORE), J8.2 (VCORE); also elsewhere on the board
/GND: C183.2, C184.2, C185.2, C186.2, C187.2, J8.3 (GND), J8.4 (GND), J8.7 (GND), J8.8 (GND), J8.13 (GND), J8.14 (GND), J8.21 (GND), J8.22 (GND), J8.29 (GND), J8.30 (GND), J8.37 (GND), J8.38 (GND), J8.45 (GND), J8.46 (GND), J8.53 (GND), J8.54 (GND), J8.61 (GND), J8.62 (GND), J8.69 (GND), J8.70 (GND), J8.77 (GND), J8.78 (GND), R96.2, U27.4 (GND), U28.10 (GND), U28.PAD (GND); also elsewhere on the board
/I2C_SCL: J8.12 (EEPROM_SCL); also elsewhere on the board
/I2C_SDA: J8.11 (EEPROM_SDA); also elsewhere on the board
/INA_ALERT: U28.3 (Alert); also elsewhere on the board
/PRSNT_2V5: J8.9 (PRESENT); also elsewhere on the board
/SUPER_I2C_SCL: U28.5 (SCL); also elsewhere on the board
/SUPER_I2C_SDA: U28.1 (A1), U28.4 (SDA); also elsewhere on the board
unnamed: C184.1, U27.6 (SR)

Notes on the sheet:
DUT_VCCIO current monitor: 0x92

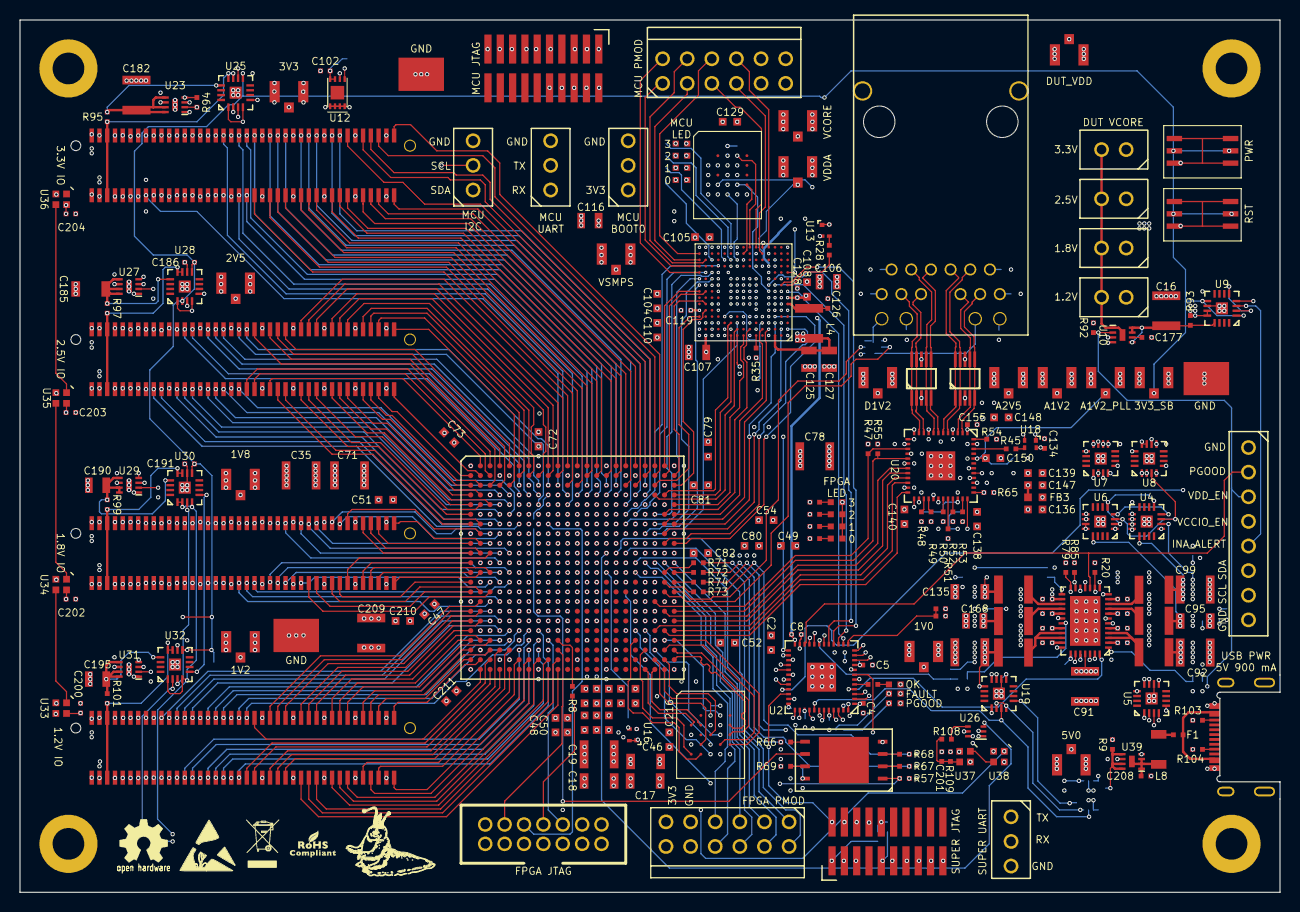
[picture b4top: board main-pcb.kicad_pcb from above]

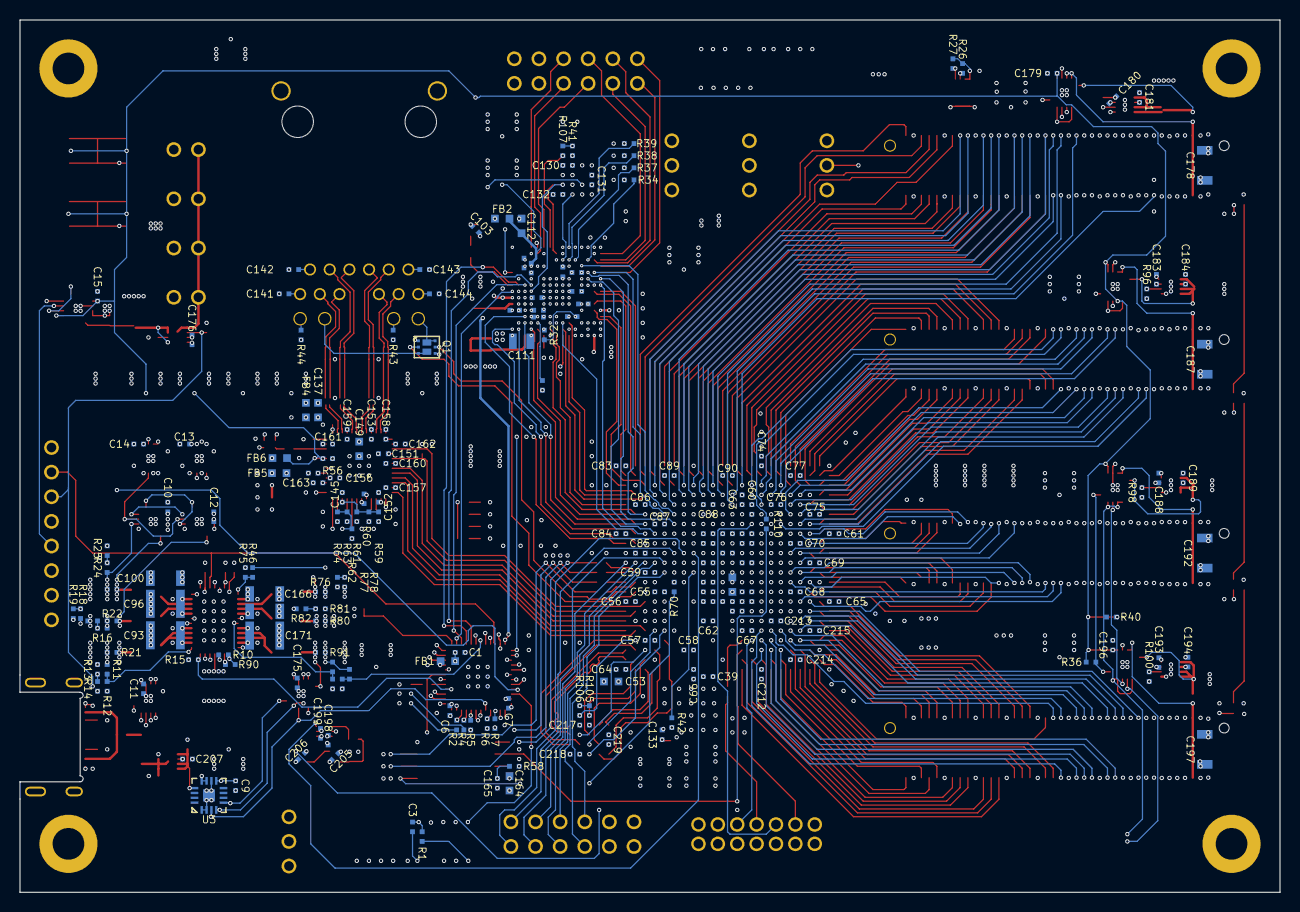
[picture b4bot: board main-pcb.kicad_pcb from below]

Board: 10 copper layers, 130.0 x 90.0 mm, 444 parts (203 on the bottom side), 492 nets.
